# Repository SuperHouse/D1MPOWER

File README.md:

Power Shield for the WeMos D1 Mini
==================================

Copyright 2016 SuperHouse Automation Pty Ltd  www.superhouse.tv  

Power supply expansion shield for the [WeMos D1 Mini][1], which is a microcontroller board based on the ESP8266 module.

Features:

 * 2.1mm DC jack and screw terminal connections for power input.
 * 5Vdc output, max 800mA.
 * 7-14Vdc nominal input range, 20Vdc max input.
 * Input polarity protection.
 * Power LED.
 * Filter caps.

More information is available at:

  http://www.superhouse.tv/d1mpower

INSTALLATION
------------
The design is saved as an EAGLE project. EAGLE PCB design software is
available from www.cadsoftusa.com free for non-commercial use. To use
this project download it and place the directory containing these files
into the "eagle" directory on your computer.

DISTRIBUTION
------------
The specific terms of distribution of this project are governed by the
license referenced below.

LICENSE
-------
Licensed under the TAPR Open Hardware License (www.tapr.org/OHL).
The "license" folder within this repository also contains a copy of
this license in plain text format.

[1]: http://www.wemos.cc/wiki/doku.php?id=en:d1_mini

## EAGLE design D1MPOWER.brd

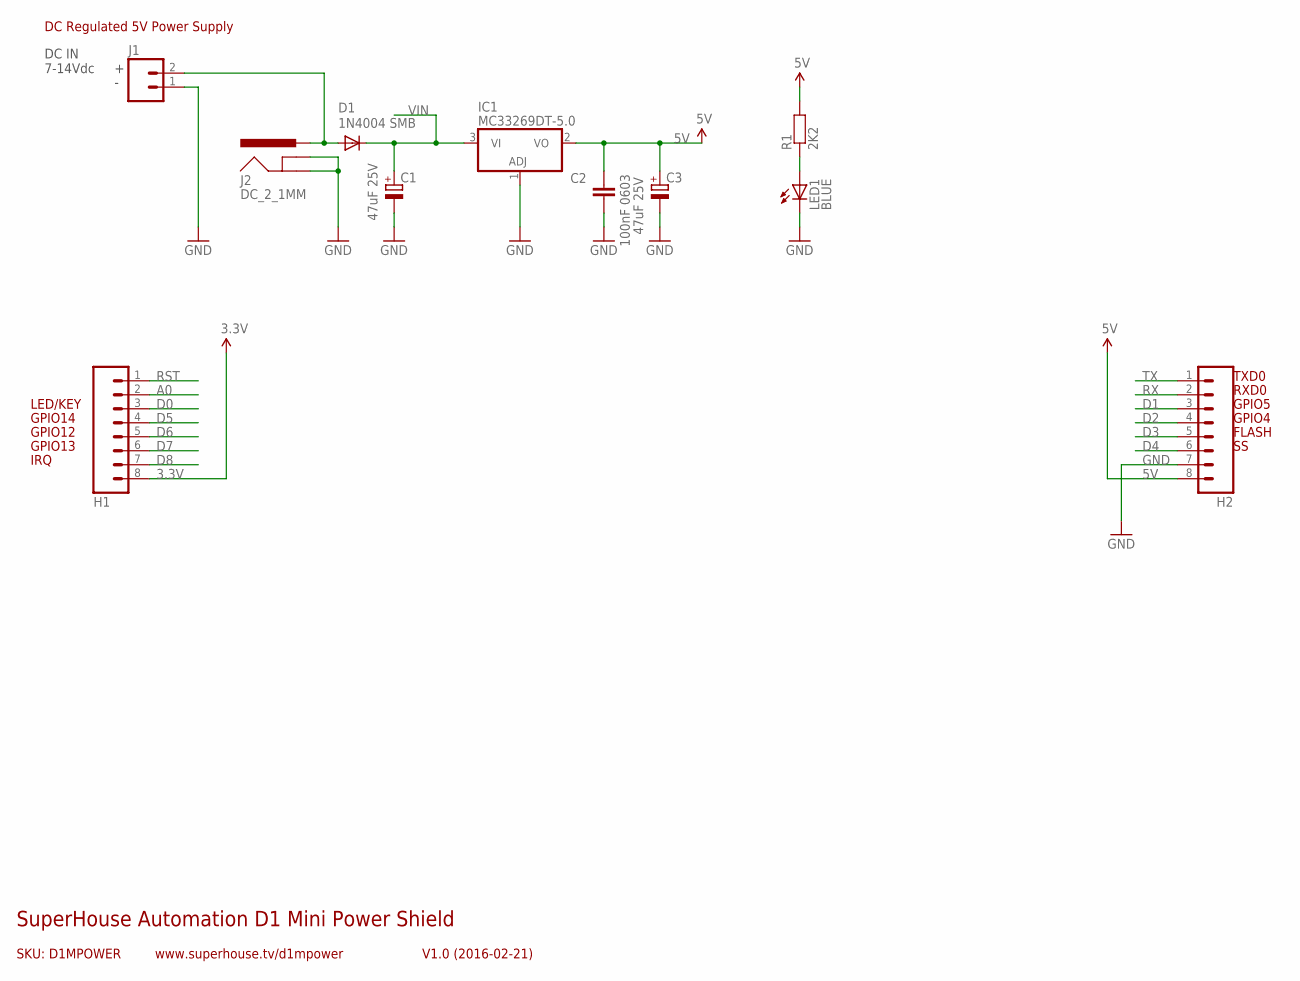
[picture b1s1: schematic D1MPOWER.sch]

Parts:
C1, C3: 47uF 25V; PANASONIC_D
C2: 100nF 0603; 0603
D1: 1N4004 SMB; SMB-DIODE
H1, H2: M08; 1X08
IC1: MC33269DT-5.0; DPACK
J1: M023.5MM; SCREWTERMINAL-3.5MM-2
J2: DC_2_1MM; POWER_JACK_PTH
LED1: BLUE; LED-0603
R1: 2K2; 0603

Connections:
3.3V: H1.8
5V: C2.1, C3.+, H2.8, IC1.2 (VO), R1.2
A0: H1.2
D0: H1.3
D1: H2.3
D2: H2.4
D3: H2.5
D4: H2.6
D5: H1.4
D6: H1.5
D7: H1.6
D8: H1.7
GND: C1.-, C2.2, C3.-, H2.7, IC1.1 (ADJ), J1.1, J2.GND, J2.GNDBREAK, LED1.C
unnamed: LED1.A, R1.1
unnamed: D1.A, J1.2, J2.PWR
RST: H1.1
RX: H2.2
TX: H2.1
VIN: C1.+, D1.C, IC1.3 (VI)

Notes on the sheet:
FLASH
GPIO12
GPIO4
GPIO5
RXD0
TXD0
GPIO13
GPIO14
IRQ
LED/KEY
SKU: D1MPOWER
SuperHouse Automation D1 Mini Power Shield
V1.0 (2016-02-21)
www.superhouse.tv/d1mpower
DC Regulated 5V Power Supply
DC IN 7-14Vdc

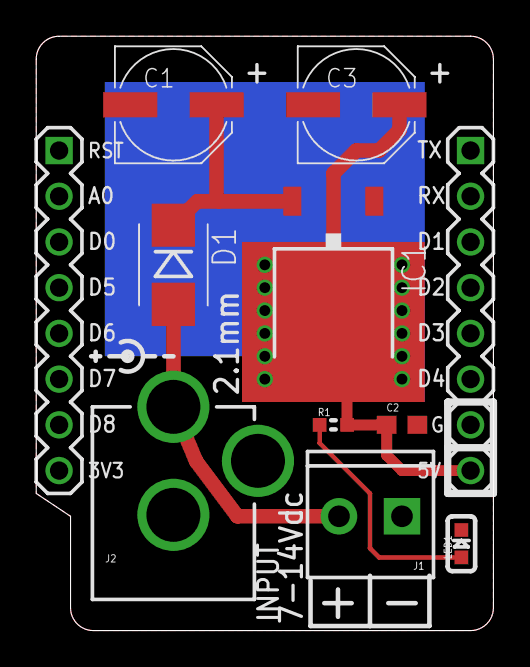
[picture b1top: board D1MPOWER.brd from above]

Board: 2 copper layers, 25.4 x 33.0 mm, 11 parts (0 on the bottom side), 5 nets.

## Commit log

2016-02-26 Initial import
2016-02-26 Added license and preview images, and updated README
2016-02-29 Optimised part designators
2016-03-02 Added photo of actual shield
2018-03-28 Improvements to labels and images

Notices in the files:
D1MPOWER.brd:
(C)2016 SuperHouse
parts and their libraries:
freetronics-original: Licensing: CC v3.0 Share-Alike You are welcome to use this library for commercial purposes.
